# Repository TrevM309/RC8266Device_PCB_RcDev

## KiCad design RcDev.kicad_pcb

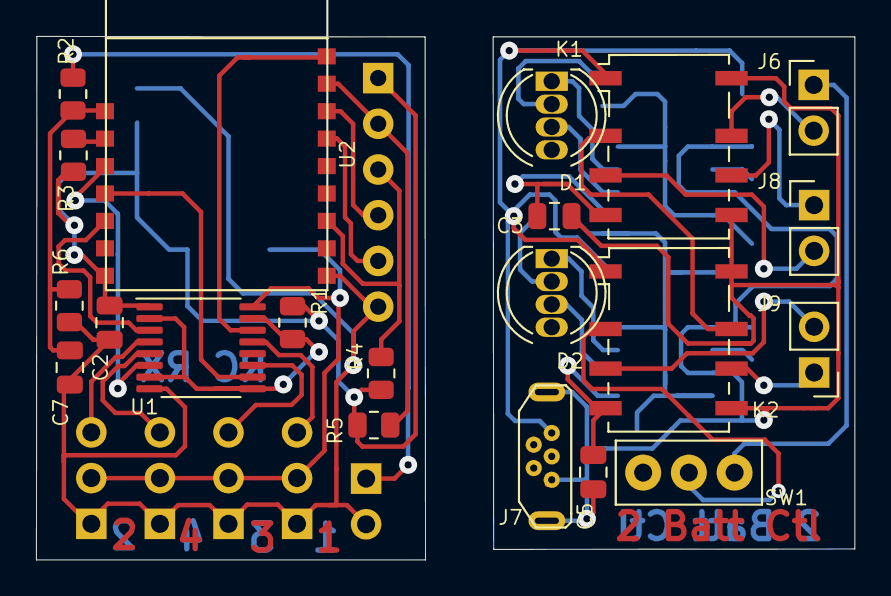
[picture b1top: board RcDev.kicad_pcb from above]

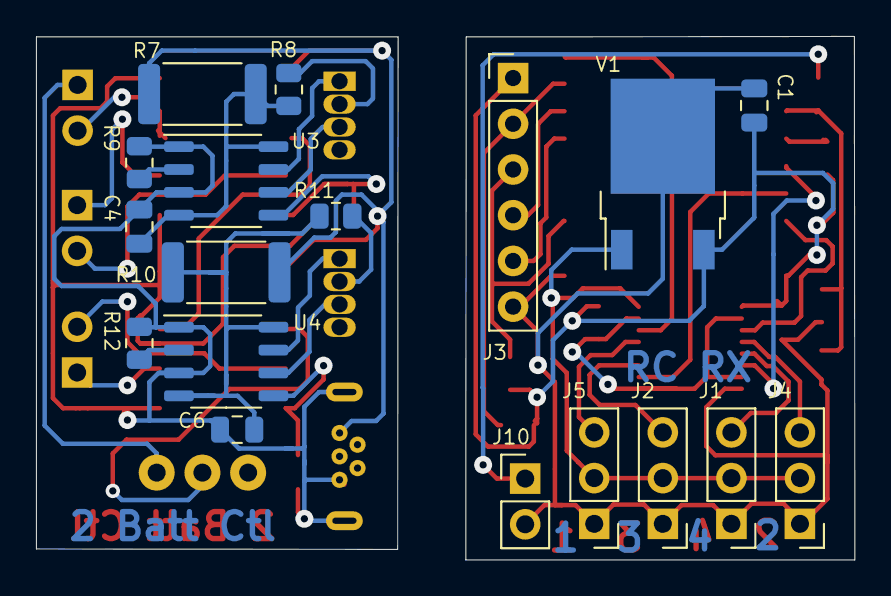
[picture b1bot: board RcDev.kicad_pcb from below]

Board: 2 copper layers, 45.5 x 29.1 mm, 39 parts (18 on the bottom side), 41 nets.

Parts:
C1, C3, C4, C5, C6: 10u; C_0805_2012Metric
C2, C7: 100n; C_0805_2012Metric
D1: Chg1; LED_D5.0mm-4_RGB
D2: Chg2; LED_D5.0mm-4_RGB
J1: Thro CH4; PinHeader_1x03_P2.54mm_Vertical
J2: Ruddr CH3; PinHeader_1x03_P2.54mm_Vertical
J3: Program; PinHeader_1x06_P2.54mm_Vertical_bent
J4: Elev CH2; PinHeader_1x03_P2.54mm_Vertical
J5: Aile CH1; PinHeader_1x03_P2.54mm_Vertical
J6: O/P 7V4; PinHeader_1x02_P2.54mm_Vertical
J7: USB; USB_micro_vertical
J8: Batt1; PinHeader_1x02_P2.54mm_Vertical
J9: Batt2; PinHeader_1x02_P2.54mm_Vertical
J10: VBatt; PinHeader_1x02_P2.54mm_Vertical
K1, K2: G6KU-2; Relay_DPDT_Omron_G6K-2F-Y
R1, R6: 1K0; R_0805_2012Metric
R2, R3, R4, R5: 10K; R_0805_2012Metric
R7, R10: R0.4; R_2512_6332Metric
R8, R9, R11, R12: 1K2; R_0805_2012Metric
SW1: On/Off; Switch_spst_pcb
U1: CD40109BPW; TSSOP-16_4.4x5mm_P0.65mm
U2: ESP-M2; ESP-M2_DOIT_sm
U3, U4: TP4056; SOP-8_3.9x4.9mm_P1.27mm
V1: BA033; TO-252-2

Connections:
+3V3: C1.1, C2.1, J3.1, R1.1, R3.1, R4.1, R5.1, U1.1, U2.7, V1.3
+BATT: J1.2, J2.2, J4.2, J5.2, U1.16, V1.1
/1+: J8.2, K1.3
/1-: J8.1, K1.6
/2+: J9.2, K2.3
/2-: J9.1, K2.6
/CH1: J5.3, U1.13
/CH2: J4.3, U1.4
/CH3: J2.3, U1.11
/CH4: J1.3, U1.5
/Flash: J3.3, R4.2, U2.10
/O+: J6.1, SW1.1
/O-: J6.2, K1.7
/RST: J3.2, R5.2, U2.15
/Rx: J3.5, U2.13
/Tx: J3.4, U2.14
GND: C1.2, C2.2, C7.2, J1.1, J2.1, J3.6, J4.1, J5.1, J10.2, R6.2, U1.8, U2.8, V1.2
GND1: C3.2, C4.2, C5.2, C6.2, J7.5, J7.6, K1.5, K1.8, K2.5, K2.8, R9.2, R12.2, U3.1, U3.3, U4.1, U4.3
unnamed: C3.1, K1.4, U3.5
unnamed: C4.1, R7.2, R8.1, U3.4, U3.8
unnamed: C5.1, K2.4, U4.5
unnamed: C6.1, R10.2, R11.1, U4.4, U4.8
unnamed: C7.1, R2.2, R6.1, U2.1
unnamed: D1.1, U3.7
unnamed: D1.2, R8.2
unnamed: D1.3, U3.6
unnamed: D2.1, U4.7
unnamed: D2.2, R11.2
unnamed: D2.3, U4.6
unnamed: J7.1, K1.1, K2.1, R7.1, R10.1
unnamed: J10.1, R2.1
unnamed: K1.2, K2.7
unnamed: K2.2, SW1.2
unnamed: R1.2, U1.2, U1.7, U1.9, U1.15
unnamed: R3.2, U2.2
unnamed: R9.1, U3.2
unnamed: R12.1, U4.2
unnamed: U1.3, U2.5
unnamed: U1.6, U2.3
unnamed: U1.10, U2.4
unnamed: U1.14, U2.16

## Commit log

2021-06-12 Etched, tracks on wrong side on USB and Bat connections, fixed
2021-06-12 Tweaks to make it more correct to assembly in 3D view (no real change to PCBs)
2021-06-19 Added 100nF capacitor to ADC
2021-06-20 Tidy up silk screens
2021-06-20 Spacing out
2021-06-21 PCB manufacture data
